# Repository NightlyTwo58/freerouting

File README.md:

## Description

Freerouting is a powerful PCB autorouter compatible with any PCB design software that supports the standard Specctra or Electra DSN interface. It imports `.dsn` files generated by the host system's Specctra interface and exports `.ses` Specctra session files.

### Commands that kinda matter

```./gradlew run``` to run build  
```./gradlew build``` to just build (will turn out .jar)

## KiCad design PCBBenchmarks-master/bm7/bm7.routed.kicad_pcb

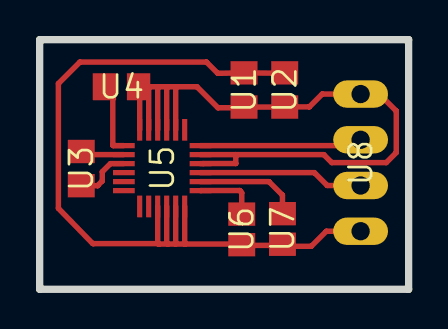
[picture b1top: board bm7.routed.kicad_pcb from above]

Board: 2 copper layers, 20.5 x 13.9 mm, 8 parts (0 on the bottom side), 9 nets.

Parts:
U1, U2, U3, U4: C0805
U5: LGA-24
U6, U7: R0805
U8: MA04-1

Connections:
/SCL: U5.21, U8.2
/SDA: U5.24, U8.3
GND: U1.2, U2.2, U4.1, U5.2, U5.3, U5.4, U5.5, U5.6, U5.22, U5.23, U8.4
unnamed: U3.1, U5.9
unnamed: U3.2, U5.8
unnamed: U4.2, U5.7
unnamed: U5.19, U6.1
unnamed: U5.20, U7.1
VDD: U1.1, U2.1, U5.15, U5.16, U5.17, U5.18, U6.2, U7.2, U8.1

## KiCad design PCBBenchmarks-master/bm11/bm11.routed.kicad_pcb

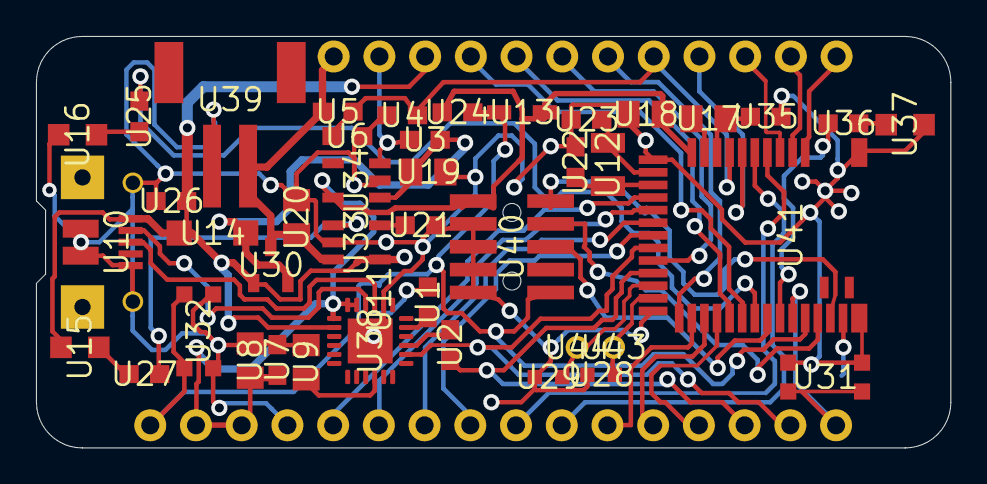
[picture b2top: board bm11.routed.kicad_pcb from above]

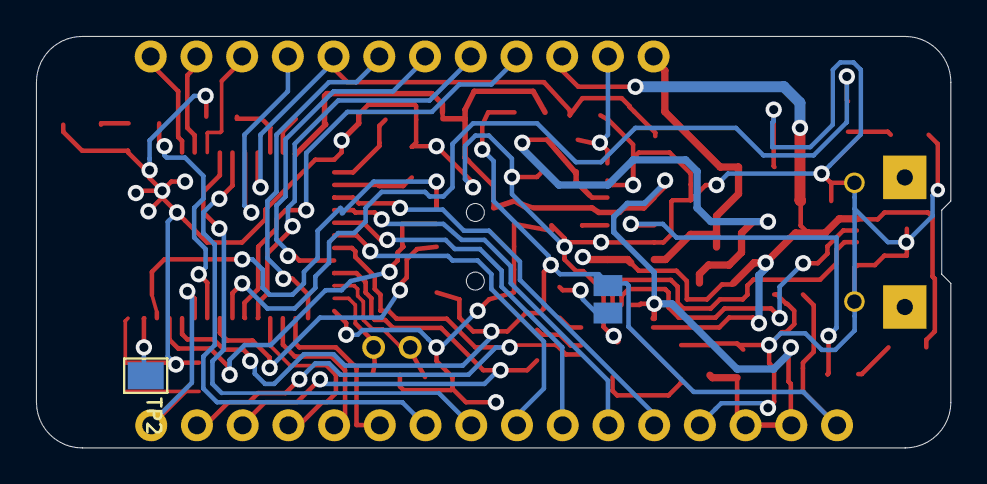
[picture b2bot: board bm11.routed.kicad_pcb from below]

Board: 2 copper layers, 50.8 x 22.9 mm, 46 parts (2 on the bottom side), 51 nets.

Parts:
MS1: MS1
MS2: MS2
TP2: FRST; PAD-1.5X2.0
U1, U2, U3, U4, U5, U6, U7, U21, U22, U23, U24, U25, U26, U27, U35, U36: 0603-NO
U8, U9, U17, U18, U19, U20: 0805-NO
U10: 4UCONN_20329_V2
U11: SOLDERJUMPER_CLOSEDWIRE
U12: XTAL3215
U13: SOD-323
U14: SOD-123
U15, U16, U37: CHIPLED_0805_NOOUTLINE
U28, U29: _0603MP
U30: SOT23-R
U31, U32: BTN_KMR2_4.6X2.8
U33, U34: SOT23-5
U38: QFN24_4MM_SMSC
U39: JSTPH2
U40: 2X05_1.27MM_BOX_POSTS
U41: BLE_MODULE_RAYTAC_MDBT42
U43, U44: 1X01_2MM

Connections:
3.3V: MS1.2, MS1.3, U7.1, U8.1, U13.C, U18.1, U24.2, U34.5, U38.5, U38.6, U38.7, U40.1, U41.11
/A0/0.02: MS1.5, U41.15
/A1/0.03: MS1.6, U41.16
/A2/0.04: MS1.7, U41.17
/A3/0.05: MS1.8, U41.18
/A4/0.28: MS1.9, U41.5
/A5/0.29: MS1.10, U41.6
/A6/P0.30: MS2.20, U41.7
/A7/P0.31: MS2.21, U4.1, U5.2, U6.1, U41.8
/DFU: MS1.16, U31.B, U31.B', U41.34
/DTR: U1.2, U38.23
/EN: MS2.27, U3.1, U34.3
/FRST: TP2.P$1, U41.38
/LED1: U25.2, U41.31
/LED2: U36.2, U41.33
/MISO: MS1.13, U41.28
/MOSI: MS1.12, U41.27
/P0.07: MS2.23, U41.20
/P0.09/NFC1: U29.1, U41.22, U44.1
/P0.10/NFC2: U28.1, U41.23, U43.1
/P0.11: MS2.22, U41.25
/P0.15: MS2.24, U41.29
/P0.16: MS2.25, U41.30
/P0.27: MS2.19, U41.4
/RESET: MS1.1, U11.1, U13.A, U24.1, U32.A, U32.A', U40.10, U41.35
/RXD: MS1.14, U2.2, U41.21
/SCK: MS1.11, U41.26
/SCL: MS2.18, U41.3
/SDA: MS2.17, U41.2
/SWCLK: U40.4, U41.36
/SWDIO: U40.2, U41.37
/SWO: U40.6, U41.32
/TXD: MS1.15, U38.20, U41.19
/USBD+: U10.D+, U38.3
/USBD-: U10.D-, U38.4
GND: MS1.4, U4.2, U6.2, U7.2, U8.2, U9.2, U10.BASE@1, U10.BASE@2, U10.GND, U10.SPRT@1, U10.SPRT@2, U16.C, U18.2, U19.2, U20.2, U21.2, U22.2, U23.2, U26.1, U28.2, U29.2, U31.A, U31.A', U32.B, U32.B', U33.2, U34.2, U35.2, U37.C, U38.2, U38.THERM, U39.1, U40.3, U40.5, U40.7, U40.9, U41.1, U41.12, U41.24, U41.39
unnamed: U12.P$1, U23.1, U41.13
unnamed: U12.P$2, U22.1, U41.14
unnamed: U17.1, U35.1, U41.9
unnamed: U3.2, U14.C, U19.1, U30.2, U34.1
unnamed: U9.1, U38.16
unnamed: U1.1, U11.2
unnamed: U15.C, U27.1
unnamed: U16.A, U25.1
unnamed: U36.1, U37.A
unnamed: U17.2, U41.10
unnamed: U27.2, U33.1
unnamed: U21.1, U33.5
unnamed: U2.1, U38.21
VBAT: MS2.28, U5.1, U20.1, U30.3, U33.3, U39.2
VBUS: MS2.26, U10.VBUS, U14.A, U15.A, U26.2, U30.1, U33.4, U38.8

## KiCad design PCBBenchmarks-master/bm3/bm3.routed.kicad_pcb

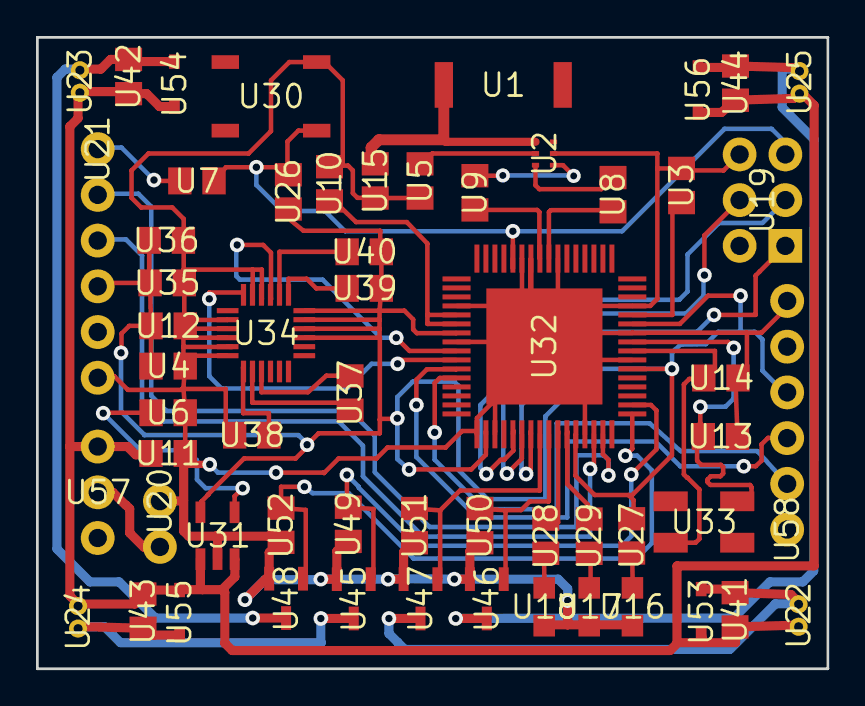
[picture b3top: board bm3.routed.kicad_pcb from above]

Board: 2 copper layers, 43.9 x 35.1 mm, 58 parts (0 on the bottom side), 44 nets.

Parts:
U1: ANTENNA-CHIP5
U2: BALUN-0805
U3, U4, U5, U6, U7, U8, U9, U10, U11, U12, U13, U14, U15, U35, U36, U37, U38, U41, U42, U43, U44: C0805
U16, U17, U18: CHIP-LED0805
U19: 2X3-NS
U20: 1X02
U21, U58: FTDI_BASIC
U22, U23, U24, U25: 653002114822
U26, U27, U28, U29, U39, U40, U49, U50, U51, U52: R0805
U30: TACTILE_SWITCH_SMD
U31: SOT23-DBV
U32: QFN-64
U33: CRYSTAL-SMD-5X3
U34: LGA-24
U45, U46, U47, U48: CONTROLLER_SOT95P237X112-3N
U53, U54, U55, U56: SOD323_ST
U57: SWITCH-SPDT

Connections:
3.3V: U4.1, U12.1, U21.VCC, U26.2, U27.2, U31.5, U32.23, U32.34, U32.44, U32.54, U32.59, U34.15, U34.16, U34.17, U34.18, U35.1, U36.1, U39.2, U40.2, U58.VCC
/MISO: U19.1, U32.39
/MOSI: U19.4, U32.38
/PB4: U32.40, U47.1, U51.1
/PB5: U32.41, U46.1, U50.1
/PB6: U28.2, U32.42
/PB7: U29.2, U32.43
/PE3: U32.49, U48.1, U52.1
/PE4: U32.50, U45.1, U49.1
/RESET: U7.2, U19.5, U26.1, U30.1, U32.12
/RFANT: U1.FEED, U2.1, U15.2
/RX0: U21.TXO, U32.46
/RX1: U32.27, U58.TXO
/SCK: U19.3, U32.37
/SCL: U32.25, U34.21
/SDA: U32.26, U34.24
/TX0: U21.RXI, U32.47
/TX1: U32.28, U58.RXI
/VBAT: U11.1, U22.1, U23.1, U24.1, U25.1, U31.1, U31.3, U41.1, U42.1, U43.1, U44.1, U53.C, U54.C, U55.C, U56.C, U57.3
GND: U2.5, U3.2, U4.2, U5.2, U6.2, U10.2, U11.2, U12.2, U13.2, U14.2, U15.1, U16.C, U17.C, U18.C, U19.6, U20.1, U21.GND, U30.3, U31.2, U32.7, U32.10, U32.11, U32.20, U32.24, U32.33, U32.35, U32.45, U32.55, U32.58, U32.61, U32.65, U34.2, U34.3, U34.4, U34.5, U34.6, U34.22, U34.23, U35.2, U36.2, U38.1, U45.2, U46.2, U47.2, U48.2, U49.2, U50.2, U51.2, U52.2, U58.GND
unnamed: U18.A, U28.1
unnamed: U2.2, U5.1
unnamed: U2.3, U8.2
unnamed: U2.4, U9.1
unnamed: U17.A, U29.1
unnamed: U3.1, U32.60
unnamed: U10.1, U32.21, U32.22
unnamed: U13.1, U32.57, U33.3
unnamed: U14.1, U32.56, U33.1
unnamed: U22.2, U41.2, U47.3, U53.A
unnamed: U23.2, U42.2, U48.3, U54.A
unnamed: U6.1, U31.4
unnamed: U24.2, U43.2, U45.3, U55.A
unnamed: U25.2, U44.2, U46.3, U56.A
unnamed: U7.1, U21.DTR
unnamed: U8.1, U32.8
unnamed: U9.2, U32.9
unnamed: U34.9, U37.1
unnamed: U34.8, U37.2
unnamed: U34.7, U38.2
unnamed: U20.2, U57.2
unnamed: U16.A, U27.1
unnamed: U34.19, U39.1
unnamed: U34.20, U40.1

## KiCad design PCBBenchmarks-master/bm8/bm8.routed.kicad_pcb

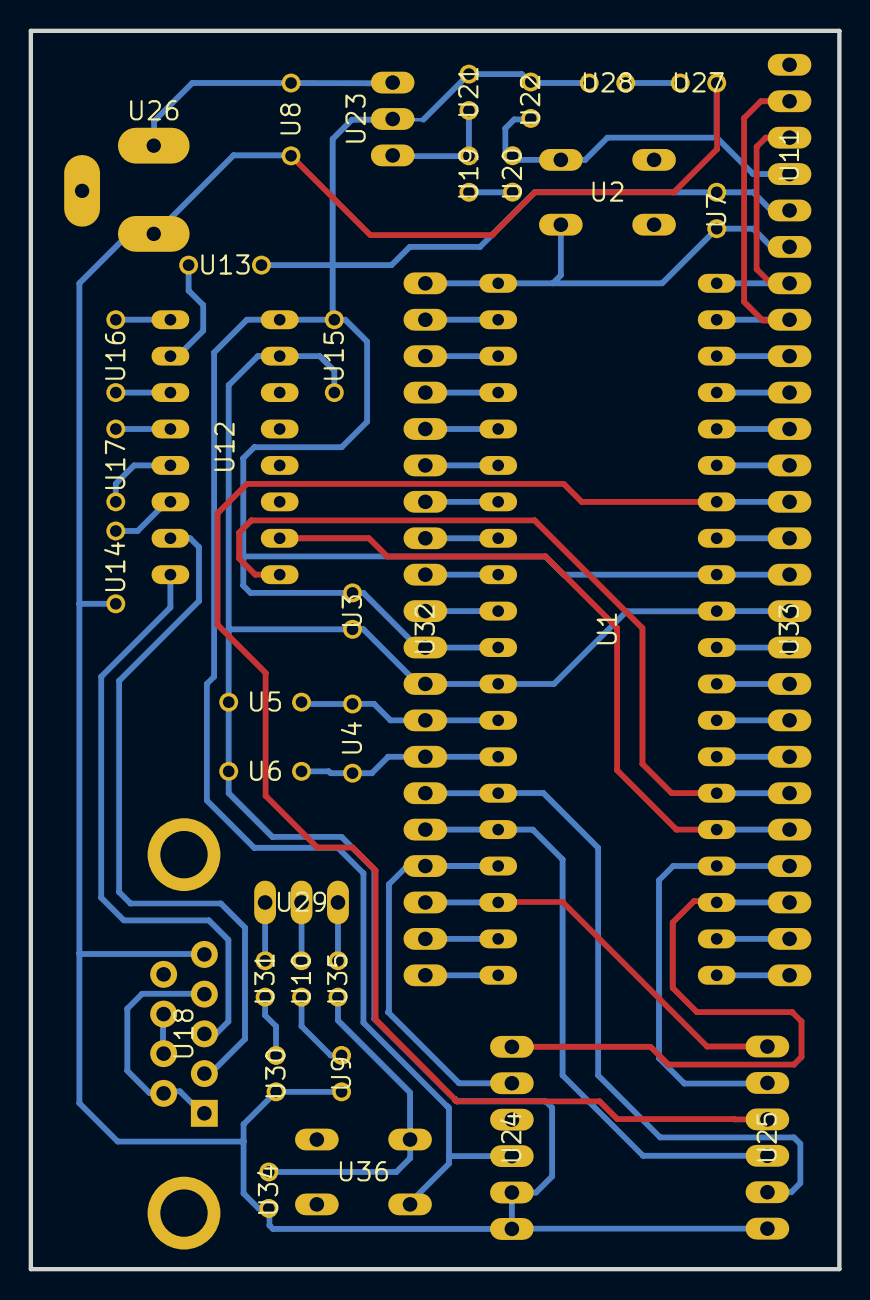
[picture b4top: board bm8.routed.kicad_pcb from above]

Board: 2 copper layers, 56.4 x 86.4 mm, 36 parts (0 on the bottom side), 58 nets.

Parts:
U1: DIL40
U2, U36: B3F-10XX
U3, U22: C025-024X044
U4: HC49_S
U5, U6, U13, U14, U15, U16, U17: C050-024X044
U7, U10, U19, U20, U21, U28, U31, U34, U35: V526-0
U8: C050-025X075
U9, U27, U30: LED3MM
U11, U24, U25: 1X06
U12: DIL16
U18: DB9
U23: 317TS
U26: 733980-62
U29: MA03-1
U32, U33: MA20-1

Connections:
/3.3V_SRC: U1.11, U1.32, U3.1, U7.1, U11.2, U12.16, U13.2, U15.1, U21.2, U22.1, U23.2, U24.3, U28.1, U32.10, U33.9, U36.1
/MRF_CS: U1.17, U24.5, U32.4
/MRF_INT: U1.34, U25.3, U33.7
/MRF_RESET: U1.15, U25.5, U32.6
/MRF_SCK: U1.18, U25.1, U32.3
/MRF_SDI: U1.23, U24.6, U33.18
/MRF_SDO: U1.24, U25.2, U33.17
/MRF_WAKE: U1.16, U25.4, U32.5
/N$17: U1.26, U12.9, U33.15
/N$21: U1.25, U12.10, U33.16
/OS1: U1.13, U4.1, U5.1, U32.8
/OSC2: U1.14, U4.2, U6.1, U32.7
GND: U1.12, U1.31, U2.1, U3.2, U5.2, U6.2, U8.2, U9.K, U11.3, U12.15, U14.1, U15.2, U18.5, U20.1, U22.2, U24.1, U24.2, U25.6, U26.1, U27.K, U30.K, U32.9, U33.10, U34.2
unnamed: U12.2, U13.1
unnamed: U12.6, U14.2
unnamed: U12.1, U16.1
unnamed: U12.3, U16.2
unnamed: U12.4, U17.1
unnamed: U12.5, U17.2
unnamed: U8.1, U23.3, U26.2
unnamed: U12.7, U18.2
unnamed: U12.8, U18.3
unnamed: U1.1, U2.3, U7.2, U11.1, U32.20
unnamed: U1.2, U32.19
unnamed: U1.3, U32.18
unnamed: U1.4, U32.17
unnamed: U1.5, U32.16
unnamed: U1.6, U32.15
unnamed: U1.7, U32.14
unnamed: U1.8, U32.13
unnamed: U1.9, U32.12
unnamed: U1.10, U32.11
unnamed: U1.19, U32.2
unnamed: U1.20, U32.1
unnamed: U1.21, U33.20
unnamed: U1.22, U33.19
unnamed: U1.27, U33.14
unnamed: U1.28, U33.13
unnamed: U1.29, U33.12
unnamed: U1.30, U33.11
unnamed: U1.33, U33.8
unnamed: U1.35, U33.6
unnamed: U1.36, U33.5
unnamed: U1.37, U33.4
unnamed: U1.38, U33.3
unnamed: U1.39, U11.5, U33.2
unnamed: U1.40, U11.4, U33.1
unnamed: U19.2, U21.1, U23.1
unnamed: U27.A, U28.2
unnamed: U30.A, U31.2
unnamed: U9.A, U10.2
unnamed: U34.1, U35.2, U36.3
unnamed: U29.3, U35.1
unnamed: U10.1, U29.2
unnamed: U29.1, U31.1
unnamed: U19.1, U20.2
unnamed: U18.1, U18.4, U18.6
unnamed: U18.7, U18.8

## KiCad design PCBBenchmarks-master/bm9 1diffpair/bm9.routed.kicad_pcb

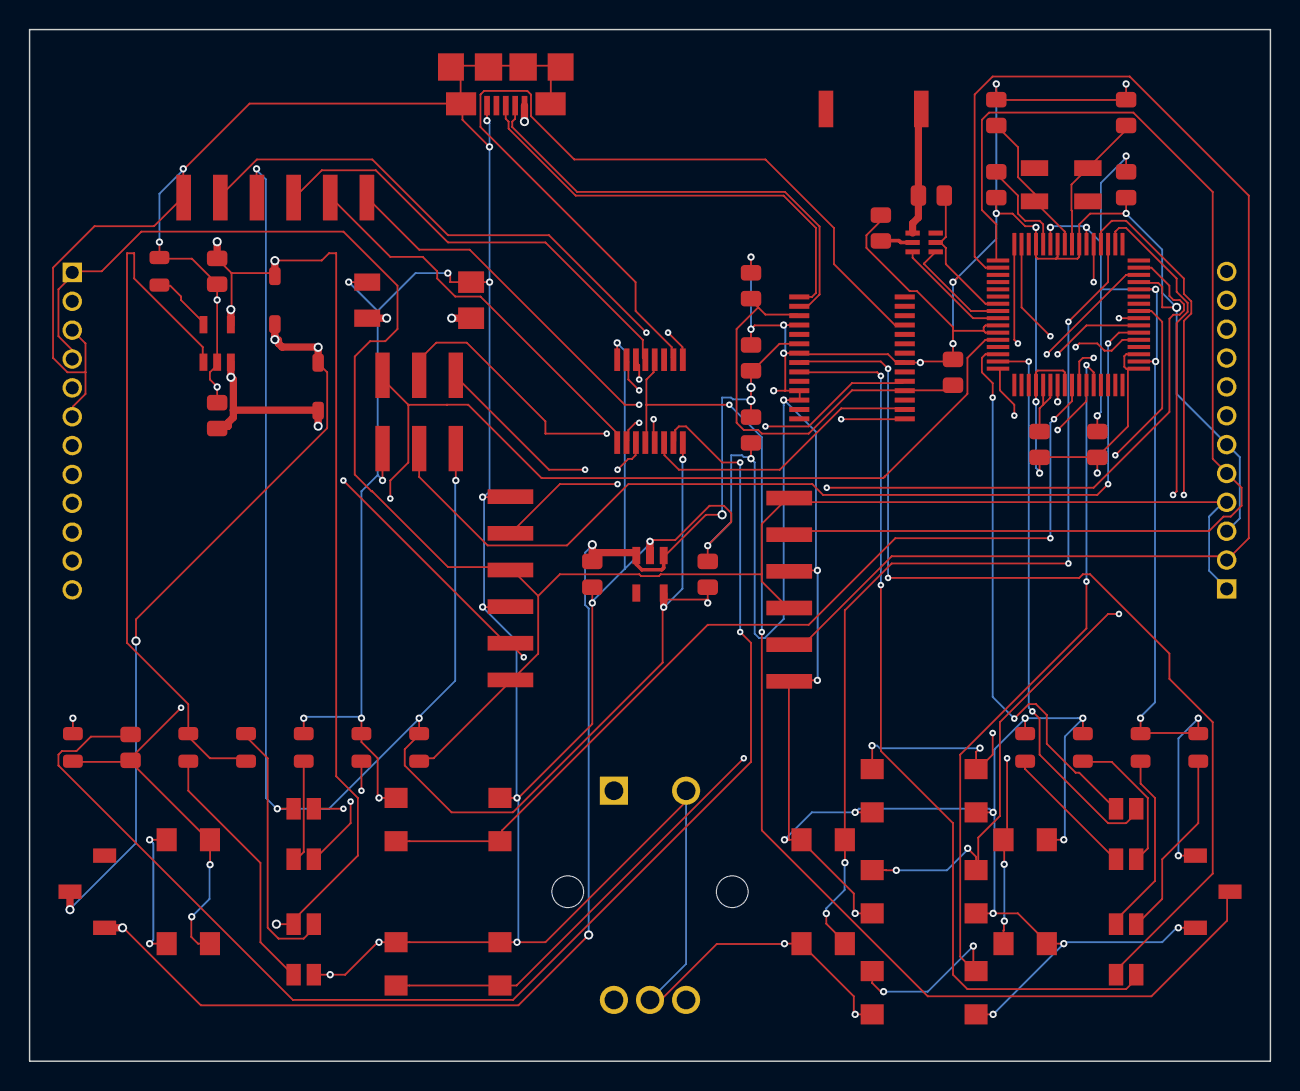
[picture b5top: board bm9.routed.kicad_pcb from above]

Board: 4 copper layers, 86.0 x 71.5 mm, 61 parts (0 on the bottom side), 63 nets.

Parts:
A1: ANTENNA-CHIP; ANT-2.4GHZ-6.5X2.2MM
B1, B4, B5, B6, B7, B8, B9, B10: PUSHBUTTON_-4.5X4.5; 4.5MM_TACTILE_SWITCH_TL3305AF160QG
B2: BALUN0805; BALUN
B3: BATTERY-SPRING-SMD; WIRE-TERMINAL-1X2-2.5MM-SMD-AVX-009276002021106
C1, C8, C9: 0.1uF; CAPC2012X140_HS
C2: 0.75pF; CAPC2012X140_HS
C3: 22pF; CAPC2012X140_HS
C4, C10, C11, C12, C13, C16, C17: 1uF; CAPC2012X140_HS
C5, C6, C7: 10uF; CAPC2012X140_HS
C14, C15: 12pF; CAPC2012X140_HS
D1, D4, D5, D6: LED-2X-GREEN_RED; LED-2X-LTST-C155
D2, D3: 360mV; SOD3716X135_HS
E1: ROTARY-ENCODER-W_BUTTON-BOURNS-PEC12R-4217F; BOURNS-PEC12R
J1: USB-MICROA-AMPHENOL-10118192-0001LF; USB-MICROA-10118192-0001LF
J2, J3: 2.4K; JST-13-PTH
J4: AVR_SPI_PRG_6-SMD; 2X3-SMD
J7, J8: FRSKY-GIMBAL-2X-SERVO-SMD; 2X-SERVO-SMD
JP1: FTDI_BASIC-SMD; FTDI-BASIC-SMD
R1, R3, R13, R14, R15, R16, R17, R18: 510; RESC2012X60_HS
R2: 10K; RESC2012X60_HS
R7: 2.2K; RESC2012X60_HS
R8: 1.2K; RESC2012X60_HS
S1, S2: POWER-SWITCH-MFS201N-9-Z-SMD-VERTICAL; JS102011JCQN
U1: 3.3V; SOT23-DBV
U2: MCP73831T-2ACI/OT; SOT23-5
U3: FT232RLSSOP; SSOP28DB
U4: ATMEGA128RFA1; QFN-64
U5: DPDT-X2; SOP65P640X110-16
Y1: CRYSTAL5X3; CRYSTAL-SMD-5X3

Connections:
3V3: C12.1, C16.1, C17.1, D4.A2, J4.2, JP1.VCC, R2.2, R8.2, R13.2, R14.2, S2.1, U1.5, U4.23, U4.34, U4.44, U4.54, U4.59, U5.16
/BTN1/SCL: B4.3, B4.4, U4.25
/BTN2/SDA: B5.3, B5.4, U4.26
/BTN_CENTER: B9.1, B9.2, U4.53
/BTN_DOWN: B10.1, B10.2, U4.28
/BTN_LEFT: B7.1, B7.2, U4.51
/BTN_RIGHT: B8.1, B8.2, U4.52
/BTN_UP: B6.1, B6.2, U4.50
/CTS: U3.11, U5.2
/CTS-1: JP1.CTS, U5.1
/DTR: U3.2, U5.14
/DTR-0: C1.2, U5.15
/DTR-1: JP1.DTR, U5.13
/E1-A: E1.A, U4.40
/E1-B: E1.B, U4.41
/E1-BUT: E1.BUTA, U4.27
/FTDI_OUT: C4.2, C9.1, U3.4, U3.17
/GREF: J2.1, J2.4, J3.1, J3.4, J7.1, J7.4, J8.1, J8.4, R8.1
/MISO: J4.1, U4.39
/MOSI: J4.4, U4.38
/PITCH: J3.V, J8.V, U4.2
/RESET: B1.1, B1.2, C1.1, J4.5, R2.1, U4.12
/RF: D4.A1, U4.16
/ROLL: J3.H, J8.H, U4.1
/RXI: U3.5, U5.10
/RXI-0: U4.47, U5.11
/RXI-1: JP1.RXI, U5.9
/RXLED: D5.C2, U3.22
/SCK: J4.3, U4.37
/THROTTLE: J2.V, J7.V, U4.64
/TXLED: D5.C1, U3.23
/TXO: U3.1, U5.6
/TXO-0: U4.46, U5.7
/TXO-1: JP1.TXO, U5.5
/USB_D_N: J1.2, U3.16
/USB_D_P: J1.3, U3.15
/VBUS: C5.1, D1.A2, D2.A, J1.1, U2.4
/VREG_IN: C7.1, C8.1, C10.1, S1.1, U1.1, U1.3, U3.20
/YAW: J2.H, J7.H, U4.63
GND: B1.3, B1.4, B2.5, B3.2A, B3.2B, B4.1, B4.2, B5.1, B5.2, B6.3, B6.4, B7.3, B7.4, B8.3, B8.4, B9.3, B9.4, B10.3, B10.4, C2.2, C3.1, C4.1, C5.2, C6.2, C7.2, C8.2, C9.2, C10.2, C11.2, C12.2, C13.2, C14.2, C15.2, C16.2, C17.2, D1.C1, E1.BUTB, E1.C, J1.5, J1.6, J1.7, J1.8, J1.9, J1.10, J1.11, J2.3, J2.6, J3.3, J3.6, J4.6, J7.3, J7.6, J8.3, J8.6, JP1.GND, R7.2, R15.1, R16.1, R17.1, R18.1, S2.3, U1.2, U2.2, U3.7, U3.18, U3.21, U3.25, U3.26, U4.7, U4.10, U4.11, U4.20, U4.24, U4.33, U4.35, U4.45, U4.55, U4.58, U4.61, U5.8
unnamed: A1.FEED, B2.1, C2.1
unnamed: B2.2, C3.2
unnamed: B2.3, U4.9
unnamed: B2.4, U4.8
unnamed: B3.1A, B3.1B, C6.1, D3.A, U2.3
unnamed: C11.1, U4.21, U4.22
unnamed: C13.1, U4.60
unnamed: C14.1, U4.57, Y1.3
unnamed: C15.1, U4.56, Y1.1
unnamed: D1.A1, R3.1
unnamed: D1.C2, R1.1
unnamed: D4.C1, R15.2
unnamed: D4.C2, R16.2
unnamed: D5.A1, R14.1
unnamed: D5.A2, R13.1
unnamed: D6.A1, U4.15
unnamed: D6.A2, U4.14
unnamed: D6.C1, R18.2
unnamed: D6.C2, R17.2
unnamed: R1.2, R3.2, U2.1
unnamed: R7.1, U2.5
unnamed: S2.2, U5.4, U5.12
VBAT: D2.C, D3.C, S1.2

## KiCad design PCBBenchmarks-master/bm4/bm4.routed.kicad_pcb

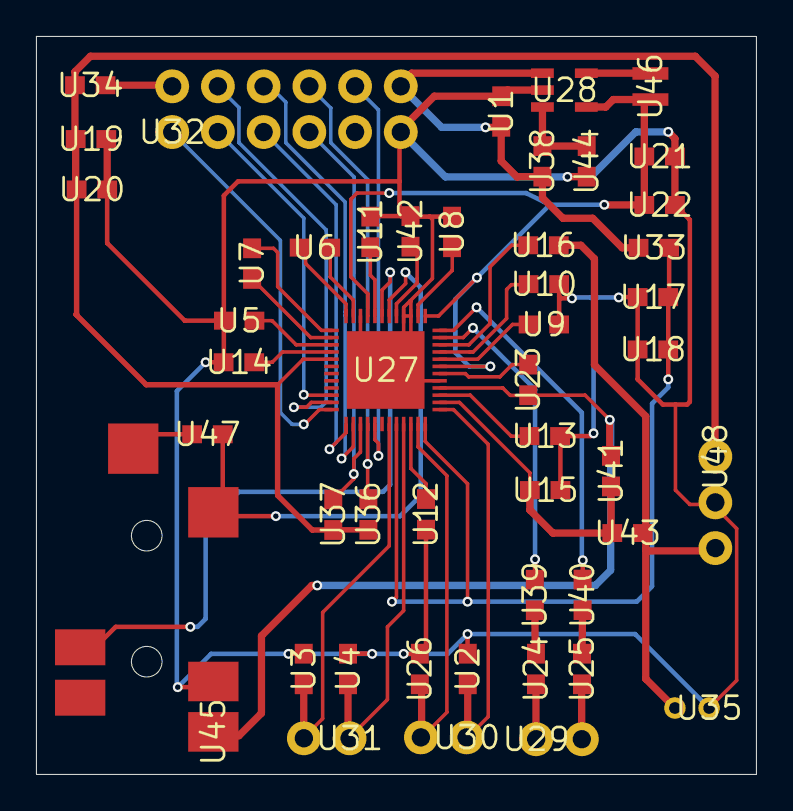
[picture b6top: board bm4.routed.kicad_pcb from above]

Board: 2 copper layers, 40.0 x 41.0 mm, 48 parts (0 on the bottom side), 47 nets.

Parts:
U1, U2, U3, U4, U5, U6, U7, U8, U9, U10, U11, U12, U13, U14, U15, U16, U17, U18, U19, U20, U21, U22, U23, U24, U25, U26, U33, U34, U36, U37, U38, U39, U40, U41, U42, U43, U44, U47: 0603
U27: QFN50P700X700X100-49N
U28: SOT95P284X122-5N
U29, U30, U31: 1X02
U32: 2X6
U35: CMC-2242PBL-A
U45: SJ-43514-SMT-TR
U46: NRH2412T2R2MNGH
U48: 1X03

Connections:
3.3V: U32.2, U34.2
5V: U1.2, U28.1, U32.12, U33.2, U38.1
/1.8VDD: U21.1, U22.1, U27.7, U27.13, U27.21, U28.4, U46.2
/3.3VDD: U19.1, U20.1, U27.29, U34.1, U36.1, U37.1, U48.1
/CPVREF: U27.17, U42.1
/HPOL: U27.18, U45.2, U47.1
/HPOR: U27.19, U45.3
/IN1P: U23.1, U27.4, U41.2, U45.1
/IN2P: U16.1, U35.2, U43.2, U48.3
/LOUTL: U27.11, U39.1
/LOUTR: U27.12, U40.1
/MICBIAS1: U15.2, U27.2, U41.1, U43.1
/SPKVDD: U17.1, U18.1, U27.44, U27.48, U33.1
/SPOLN: U26.1, U27.47, U30.2
/SPOLP: U2.1, U27.1, U30.1
/SPORN: U3.1, U27.43, U31.2
/SPORP: U4.1, U27.45, U31.1
/XADUIO_I2S0_BCLK: U27.37, U32.5
/XADUIO_I2S0_LRCKL: U27.36, U32.1
/XADUIO_SCL: U27.39, U32.7, U37.2
/XAUDIO_I2S0_DIN: U27.35, U32.4
/XAUDIO_I2S0_DOUT: U27.34, U32.3
/XAUDIO_I2S0_MCLK: U27.38, U32.6
/XAUDIO_IRQ: U27.41, U32.10
/XAUDIO_SDA: U27.40, U32.8, U36.2
GND: U1.1, U2.2, U3.2, U4.2, U5.2, U8.1, U9.1, U10.1, U11.2, U12.1, U13.1, U14.1, U15.1, U17.2, U18.2, U19.2, U20.2, U21.2, U22.2, U26.2, U27.5, U27.15, U27.16, U27.22, U27.49, U28.2, U32.11, U35.1, U42.2, U44.1, U45.4, U48.2
unnamed: U11.1, U27.20
unnamed: U23.2, U27.6
unnamed: U24.1, U39.2
unnamed: U24.2, U29.1
unnamed: U25.1, U40.2
unnamed: U25.2, U29.2
unnamed: U5.1, U27.27
unnamed: U6.1, U27.24
unnamed: U6.2, U27.23
unnamed: U7.1, U27.25
unnamed: U7.2, U27.26
unnamed: U8.2, U27.14
unnamed: U9.2, U27.8
unnamed: U10.2, U27.9
unnamed: U12.2, U27.46
unnamed: U13.2, U27.3
unnamed: U14.2, U27.28
unnamed: U16.2, U27.10
unnamed: U28.3, U38.2, U44.2
unnamed: U28.5, U46.1
unnamed: U45.5, U47.2

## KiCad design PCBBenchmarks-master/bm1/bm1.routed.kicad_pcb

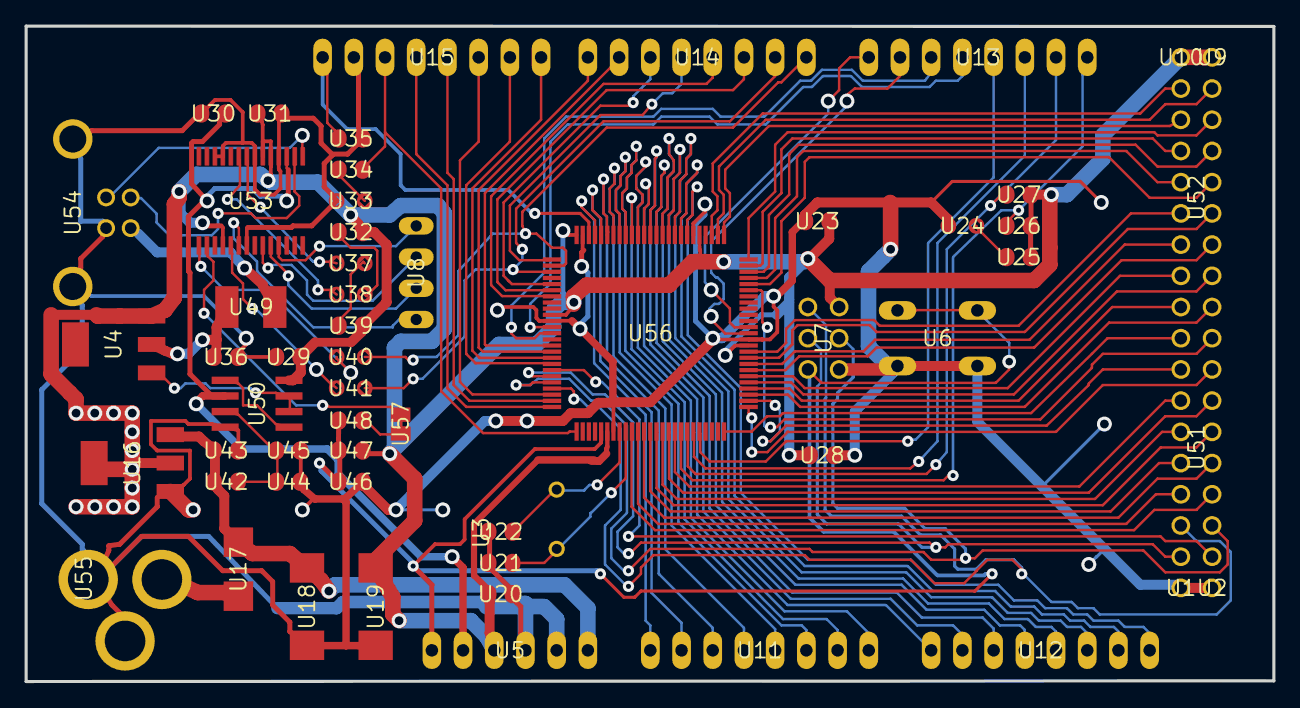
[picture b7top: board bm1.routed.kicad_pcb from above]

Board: 2 copper layers, 101.5 x 53.3 mm, 57 parts (0 on the bottom side), 99 nets.

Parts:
U1, U2, U9, U10: 1X01
U3: HC49_S
U4, U16: SOT223
U5: 1X06
U6: B3F-10XX
U7: 2X03
U8: JP4
U11, U12, U13, U14, U15: 1X08
U17: SMB
U18, U19: SMC_D
U20, U21, U22, U23, U28, U29, U30, U31, U35, U36, U43, U44, U46, U48: C0805RND
U24, U33, U37, U38: 0805RND
U25, U26, U27, U32, U34, U39, U42, U45, U47: R0805RND
U40, U41: RCL_0805RND
U49: L1812
U50: SO08
U51, U52: 2X08
U53: SSOP28
U54: PN61729
U55: DC-21MM
U56: TQFP100
U57: SJ

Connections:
+3V3: U5.2, U30.2, U50.2, U53.17
+5V: U4.3, U5.3, U7.2, U9.1, U10.1, U16.2, U16.4, U19.+, U20.1, U23.1, U25.1, U26.1, U27.1, U28.1, U29.2, U31.1, U32.2, U39.2, U47.2, U50.8, U53.4, U53.19, U53.20, U56.10, U56.31, U56.61, U56.80, U56.100
ADC0: U11.1, U56.97
ADC1: U11.2, U56.96
ADC2: U11.3, U56.95
ADC3: U11.4, U56.94
ADC4: U11.5, U56.93
ADC5: U11.6, U56.92
ADC6: U11.7, U56.91
ADC7: U11.8, U56.90
ADC8: U12.1, U56.89
ADC9: U12.2, U56.88
ADC10: U12.3, U56.87
ADC11: U12.4, U56.86
ADC12: U12.5, U56.85
ADC13: U12.6, U56.84
ADC14: U12.7, U56.83
ADC15: U12.8, U56.82
AREF: U15.8, U35.1, U56.98
CMP: U42.1, U44.2, U45.2, U50.3
CTS: U8.1, U53.11
D+: U53.15, U54.3
D-: U53.16, U54.2
DCD: U8.3, U53.10
DSR: U8.2, U53.9
DTR: U48.1, U53.2, U57.1, U57.2
GATE_CMD: U4.1, U50.6, U50.7
GND: U1.1, U2.1, U5.4, U5.5, U6.1, U6.2, U7.6, U15.7, U16.1, U18.-, U19.-, U20.2, U21.1, U22.1, U23.2, U24.P$2, U28.2, U29.1, U30.1, U31.2, U33.P$2, U35.2, U36.2, U43.2, U44.1, U45.1, U46.2, U50.4, U53.7, U53.18, U53.21, U53.25, U53.26, U54.4, U54.P$1, U54.P$2, U55.1, U55.3, U56.11, U56.32, U56.62, U56.81, U56.99
M8RXD: U40.P$1, U53.1
M8TXD: U41.P$1, U53.5
unnamed: U33.P$1, U34.2
unnamed: U24.P$1, U25.2
unnamed: U50.1, U50.5
unnamed: U3.1, U21.2, U56.34
unnamed: U3.2, U22.2, U56.33
unnamed: U38.P$2, U53.23
unnamed: U37.P$2, U53.22
unnamed: U32.1, U38.P$1
unnamed: U37.P$1, U39.1
unnamed: U49.2, U54.1
PA0: U52.16, U56.78
PA1: U52.15, U56.77
PA2: U52.14, U56.76
PA3: U52.13, U56.75
PA4: U52.12, U56.74
PA5: U52.11, U56.73
PA6: U52.10, U56.72
PA7: U52.9, U56.71
PB0: U51.1, U56.19
PB1: U7.3, U51.2, U56.20
PB2: U7.4, U51.3, U56.21
PB3: U7.1, U51.4, U56.22
PB4: U15.3, U56.23
PB5: U15.4, U56.24
PB6: U15.5, U56.25
PB7: U15.6, U34.1, U56.26
PC0: U52.1, U56.53
PC1: U52.2, U56.54
PC2: U52.3, U56.55
PC3: U52.4, U56.56
PC4: U52.5, U56.57
PC5: U52.6, U56.58
PC6: U52.7, U56.59
PC7: U52.8, U56.60
PD7: U51.16, U56.50
PE0: U14.1, U40.P$2, U56.2
PE1: U14.2, U41.P$2, U56.3
PE3: U14.6, U56.5
PE4: U14.3, U56.6
PE5: U14.4, U56.7
PG0: U51.13, U56.51
PG1: U51.14, U56.52
PG2: U51.15, U56.70
PG5: U14.5, U56.1
PH3: U14.7, U56.15
PH4: U14.8, U56.16
PH5: U15.1, U56.17
PH6: U15.2, U56.18
PL0: U51.5, U56.35
PL1: U51.6, U56.36
PL2: U51.7, U56.37
PL3: U51.8, U56.38
PL4: U51.9, U56.39
PL5: U51.10, U56.40
PL6: U51.11, U56.41
PL7: U51.12, U56.42
PWRIN: U17.A, U55.2
RESET: U5.1, U6.3, U6.4, U7.5, U46.1, U47.1, U48.2, U56.30
RI: U8.4, U53.6
RXD1: U13.3, U56.45
RXD2: U13.5, U56.12
RXD3: U13.7, U56.63
SCL: U13.1, U26.2, U56.43
SDA: U13.2, U27.2, U56.44
TXD1: U13.4, U56.46
TXD2: U13.6, U56.13
TXD3: U13.8, U56.64
USBVCC: U4.2, U36.1, U49.1
VIN: U5.6, U16.3, U17.C, U18.+, U42.2, U43.1

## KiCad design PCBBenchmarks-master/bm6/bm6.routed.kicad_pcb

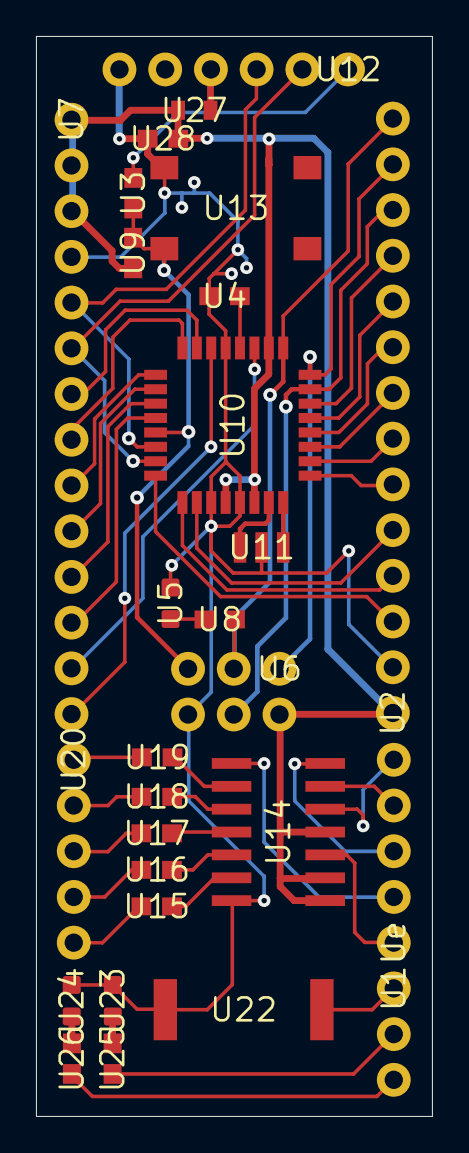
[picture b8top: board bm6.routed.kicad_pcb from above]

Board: 2 copper layers, 22.0 x 60.0 mm, 28 parts (0 on the bottom side), 51 nets.

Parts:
U1: 1X03
U2, U7: 1X14
U3, U4, U8, U9, U15, U16, U17, U18, U19, U25, U26, U28: 0603
U5, U23, U24: LED-0603
U6: 2X3
U10: TQFP32-08
U11: RESONATOR-SMD
U12: FTDI_BASIC
U13: TACTILE_SWITCH_SMD_6.2MM_TALL
U14: SO14
U20: 1X05
U22: PKMCS
U27: FUSC1608X100N
Ue: 1X05

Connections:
/A0: U7.7, U10.23
/A1: U7.8, U10.24
/A2: U7.9, U10.25
/A3: U7.10, U10.26
/A4: U7.11, U10.27
/A5: U7.12, U10.28
/A6: U7.13, U10.19
/A7: U7.14, U10.22
/D2: U2.3, U10.32
/D3: U2.4, U10.1
/D4: U2.5, U10.2
/D5: U2.6, U10.9
/D6: U2.7, U10.10
/D7: U2.8, U10.11
/D8: U2.9, U10.12
/D9: U2.10, U10.13
/D10: U2.11, U10.14
/DTR: U3.1, U12.DTR
/GO: U14.3, Ue.1
/MISO: U2.13, U6.1, U10.16
/MOSI: U2.12, U6.4, U10.15
/OUT1: U14.8, Ue.2
/OUT2: U14.7, Ue.3
/OUT3: U14.6, Ue.4
/OUT4: U14.5, Ue.5
/RST: U3.2, U6.5, U9.1, U10.29, U13.B2
/RXI: U7.5, U10.30, U12.TXO
/SCK: U2.14, U6.3, U8.1, U10.17
/TXO: U7.6, U10.31, U12.RXI
GND: U2.2, U4.2, U5.C, U6.6, U7.4, U10.3, U10.5, U10.21, U11.2, U12.GND, U13.A2, U14.14, U22.1, U23.C, U24.C, U28.2
unnamed: U4.1, U10.20
unnamed: U5.A, U8.2
unnamed: U23.A, U25.1
unnamed: U24.A, U26.1
unnamed: U12.VCC, U27.1
unnamed: U14.9, U19.2
unnamed: U14.10, U18.2
unnamed: U14.11, U17.2
unnamed: U14.12, U16.2
unnamed: U14.13, U15.2
unnamed: U19.1, U20.1
unnamed: U18.1, U20.2
unnamed: U17.1, U20.3
unnamed: U16.1, U20.4
unnamed: U15.1, U20.5
unnamed: U1.1, U22.2
unnamed: U1.2, U25.2
unnamed: U1.3, U26.2
unnamed: U10.7, U11.3
unnamed: U10.8, U11.1
VCC: U2.1, U6.2, U7.1, U7.2, U7.3, U9.2, U10.4, U10.6, U10.18, U14.1, U14.2, U14.4, U27.2, U28.1

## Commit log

2026-06-28 Intelligent Ripups
    - remembers what nets (not PCB board components yet) conflict when autoroute fails, so retries routing intelligently (i.e. if nothing changed, it won't try ripup again)
    - benchmarking suite
2026-06-29 CDCL, area, scores
2026-06-29 Looser Retry Mechanics
2026-06-29 (#2) Benchmarking Script
